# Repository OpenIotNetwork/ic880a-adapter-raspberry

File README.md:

What is it?
-----------
This adapter board connects a Raspberry Pi (Zero, 2 Model B or above) to an IMST iC880A LoRaWAN concentrator board.  
You can use the board instead of jumper wires which makes the work much easier.  
Power is provided by Raspberry Pi.

What you find here
------------------
- KiCad Fils
- Gerber Files
- Pictures of the iC880A-Adapter-Board

iC880A-Adapter-Board
--------------------
It is easy to build the board. You need to solder the following parts to complete it:
- 1 pc of 1x20 pinheader
- 1 pc of 2x20 pinheader
- 2 pcs of 1x3 pinheader

Pinout
------
iC880A <-> Raspberry Pi
- 07 <-> 38 ... GPIO20
- 08 <-> 36 ... GPIO16
- 09 <-> 32 ... GPIO12
- 10 <-> 31 ... GPIO6
- 11 <-> 29 ... GPIO5
- 13 <-> 22 ... GPIO25-Reset
- 14 <-> 23 ... GPIO11-CLK
- 15 <-> 21 ... GPIO9-MISO
- 16 <-> 19 ... GPIO10-MOSI
- 17 <-> 24 ... GPIO8-NSS
- 21 <-> 02 ... 5V-VCC

LoRaWAN-Gateway
---------------
To build a LoRaWAN-Gateway you need just a
- Raspberry Pi (Zero, 2 Model B or above) + power supply
- this iC880A-Adapter-Board
- IMST iC880A LoRaWAN concentrator board
- antenna + cable

Setup the LoRaWAN-Gateway
-------------------------
To set up the software on your LoRaWAN-Gateway, see setup scripts at https://github.com/OpenIotNetwork/ic880a-setup-scripts

Info
----
You find information about our LoRaWAN initiative at https://openiot.network  
See also OpenIoT-Forum at https://forum.openiot.network/t/openiot-ic880a-adapter-board/112

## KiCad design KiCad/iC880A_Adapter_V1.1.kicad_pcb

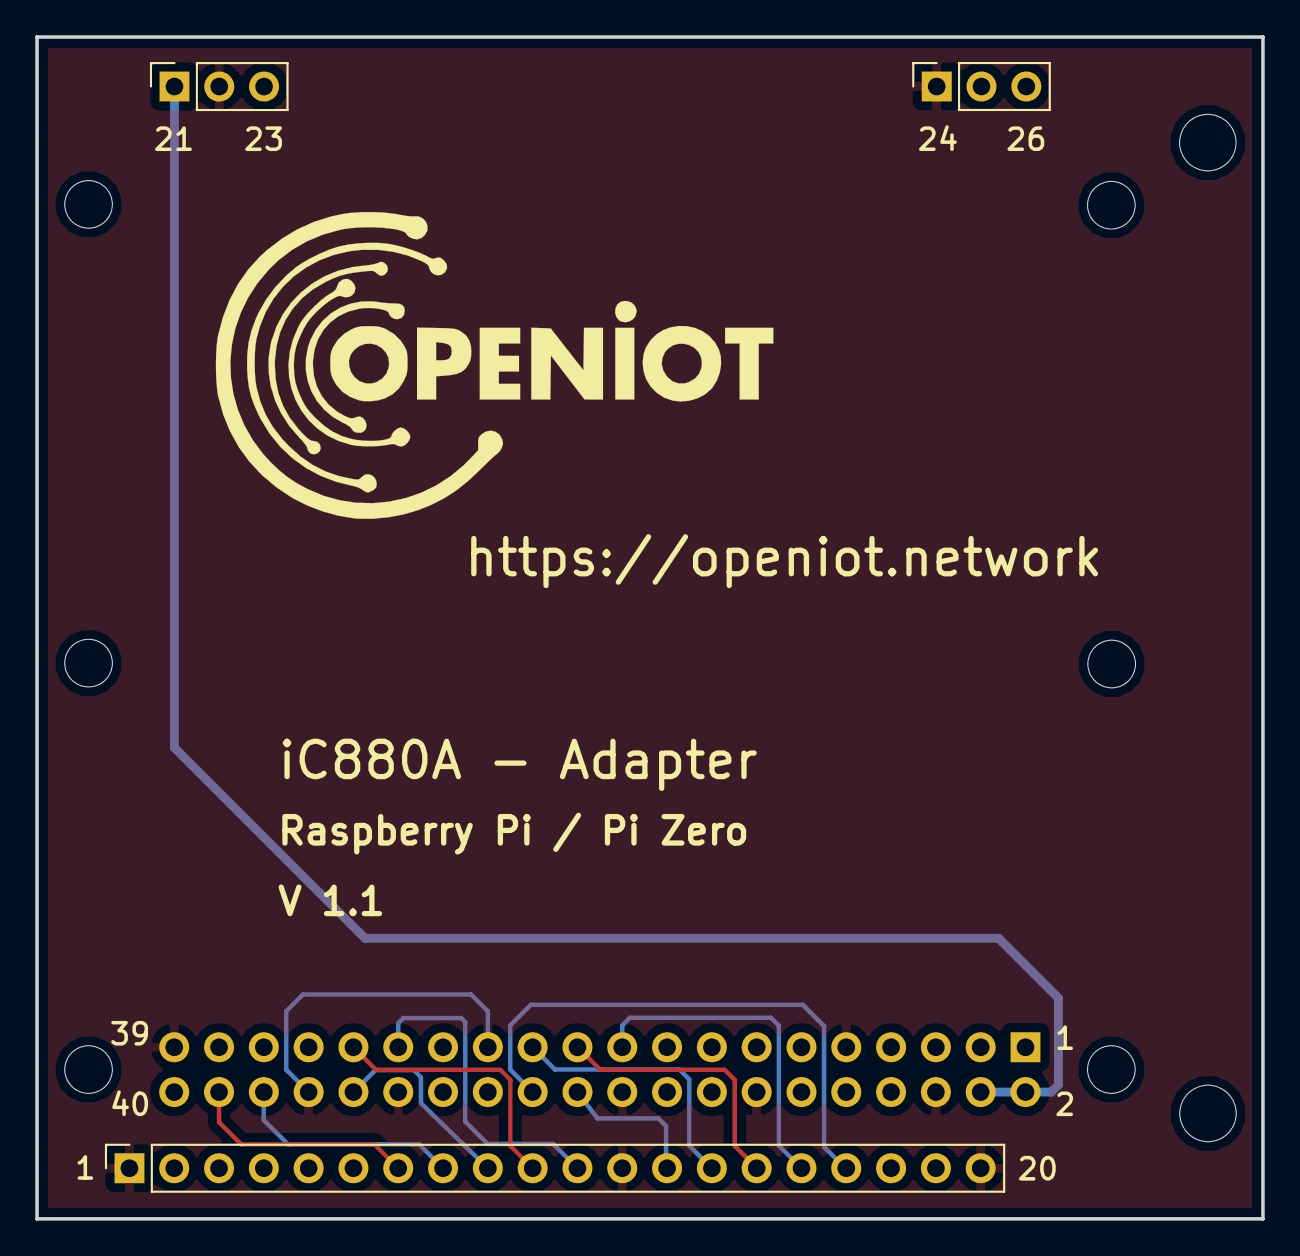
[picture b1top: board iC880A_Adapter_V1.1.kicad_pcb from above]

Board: 2 copper layers, 69.5 x 67.0 mm, 4 parts (1 on the bottom side), 12 nets.

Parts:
J1: Raspberry PI Header; PinSocket_2x20_P2.54mm_Vertical
J2: iC880 Header 1x20; PinSocket_1x20_P2.54mm_Vertical
J3: iC880 Header 1x3 (21-23); PinSocket_1x03_P2.54mm_Vertical
J4: iC880 Header 1x3 (24-26); PinSocket_1x03_P2.54mm_Vertical

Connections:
+5V: J1.2, J1.4, J3.1
GND: J1.6, J1.9, J1.14, J1.20, J1.25, J1.30, J1.34, J1.39, J2.1, J2.12, J2.20, J3.2, J4.1
GPIO5: J1.29, J2.11
GPIO6: J1.31, J2.10
GPIO8_SPI0_CS0: J1.24, J2.17
GPIO9_SPI0_MISO: J1.21, J2.15
GPIO10_SPI0_MOSI: J1.19, J2.16
GPIO11_SPI0_SCLK: J1.23, J2.14
GPIO12: J1.32, J2.9
GPIO16: J1.36, J2.8
GPIO20: J1.38, J2.7
GPIO25: J1.22, J2.13

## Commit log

2019-04-18 Create README.md
    initial commit
2019-04-18 Update README.md
    link to forum
2019-04-18 iC880A_Adapter_V1.1
2019-04-18 Create LICENSE
2019-04-20 README.md
